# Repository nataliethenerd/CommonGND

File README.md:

# CommonGND
These are for PERSONAL USE ONLY. Free use in any personal project.
<br>My logo must be kept on the boards and on any boards adapted with them and full credit must be given. AKA read the licence (https://creativecommons.org/licenses/by-nc-sa/3.0/)
<br>Enjoy :)

## New Gameboy Pocket IO Boards
> Contribution Added by [@32teeth](https://github.com/32teeth) from [@retro-esp32](https://github.com/retro-esp32)

See [Licence](LICENCE.md) and [Code of Conduct](CODE_OF_CONDUCT.md)

| |W/O Audio | Audio |
|-|-|-|
|Top | | |
|Bottom | | |

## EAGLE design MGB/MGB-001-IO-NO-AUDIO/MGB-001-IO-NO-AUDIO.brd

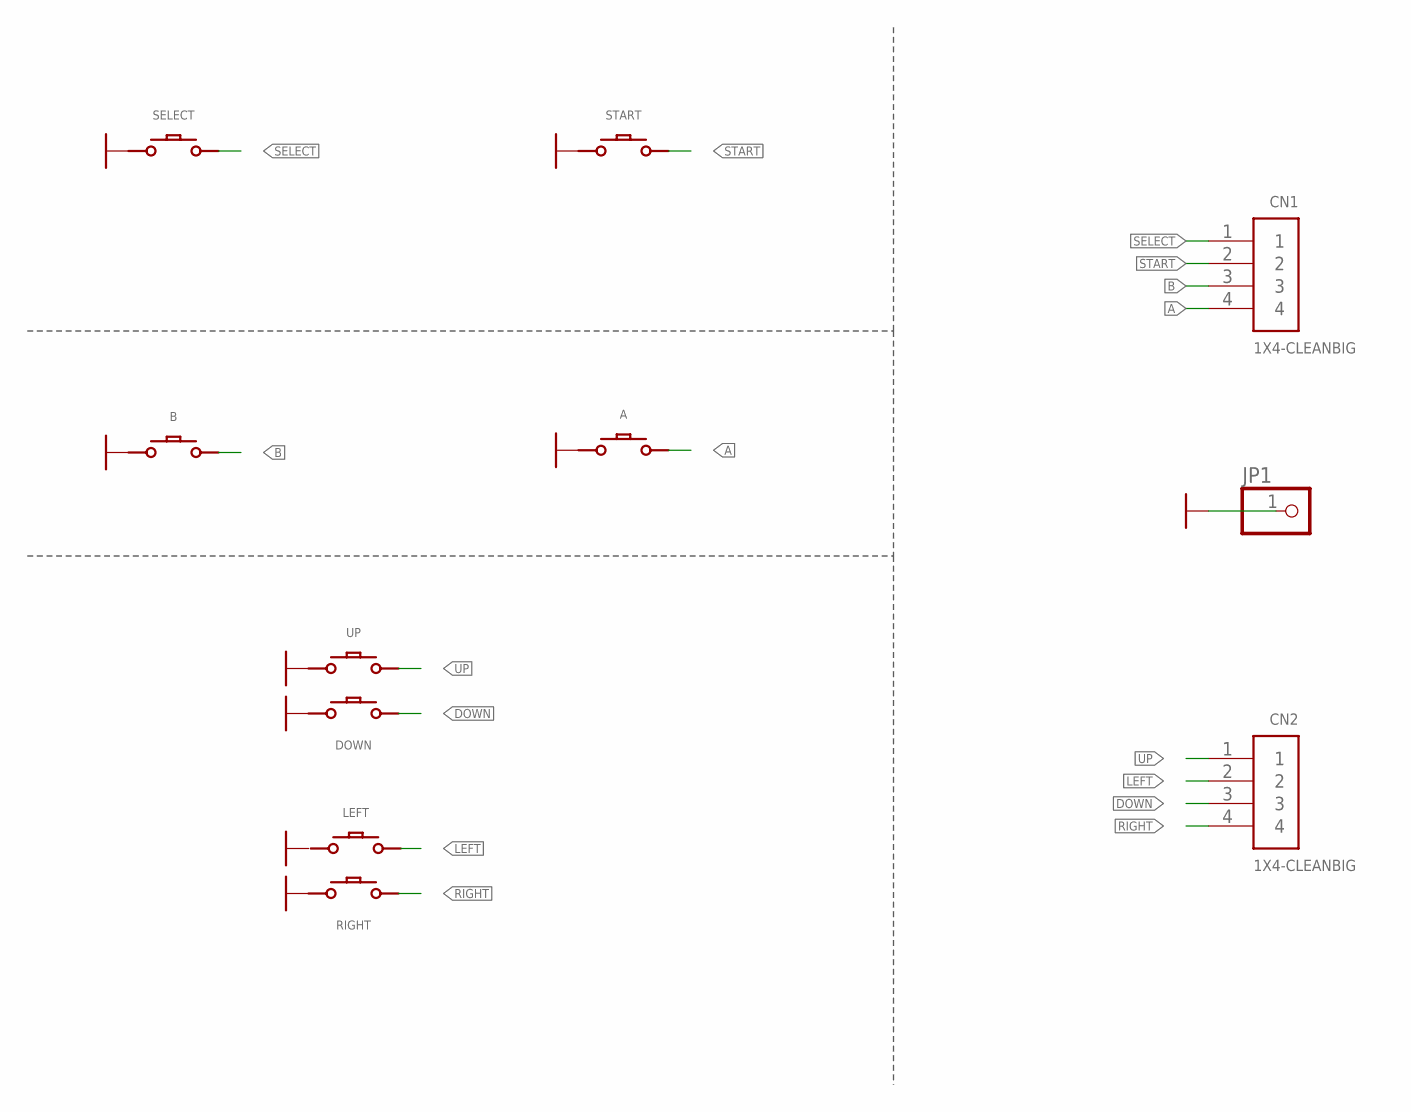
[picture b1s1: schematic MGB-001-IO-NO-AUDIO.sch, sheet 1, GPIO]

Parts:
A: CONDUCTIVE_BUTTONCONDUCTIVE_BUTTON_THICK; CONDUCTIVE_BUTTON_THICK
B: CONDUCTIVE_BUTTONCONDUCTIVE_BUTTON_THICK; CONDUCTIVE_BUTTON_THICK
CN1, CN2: 1X4-CLEANBIG; 1X04-CLEANBIG
DOWN: CONDUCTIVE_BUTTONCONDUCTIVE_BUTTON_DIRECTIONAL_TH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; CONDUCTIVE_BUTTON_DIRECTIONAL_THICK
JP1: PINHD-1X1CB; 1X01-CLEANBIG
LEFT: CONDUCTIVE_BUTTONCONDUCTIVE_BUTTON_DIRECTIONAL_TH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; CONDUCTIVE_BUTTON_DIRECTIONAL_THICK
RIGHT: CONDUCTIVE_BUTTONCONDUCTIVE_BUTTON_DIRECTIONAL_TH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; CONDUCTIVE_BUTTON_DIRECTIONAL_THICK
SELECT: CONDUCTIVE_BUTTON_STARTSELECTCONDUCTIVE_BUTTON_TH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; CONDUCTIVE_BUTTON_THICK_STARTSELECT
START: CONDUCTIVE_BUTTON_STARTSELECTCONDUCTIVE_BUTTON_TH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; CONDUCTIVE_BUTTON_THICK_STARTSELECT
UP: CONDUCTIVE_BUTTONCONDUCTIVE_BUTTON_DIRECTIONAL_TH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; CONDUCTIVE_BUTTON_DIRECTIONAL_THICK

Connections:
A: A.P$ACTIVE, CN1.4
B: B.P$ACTIVE, CN1.3
DOWN: CN2.3, DOWN.P$ACTIVE
GND: A.P$GND, B.P$GND, DOWN.P$GND, JP1.1, RIGHT.P$GND, SELECT.P$GND, SELECT.P$GND1 (P$GND), SELECT.P$GND2 (P$GND), SELECT.P$GND3 (P$GND), START.P$GND, START.P$GND1 (P$GND), START.P$GND2 (P$GND), START.P$GND3 (P$GND), UP.P$GND
LEFT: CN2.2, LEFT.P$ACTIVE
RIGHT: CN2.4, RIGHT.P$ACTIVE
SELECT: CN1.1, SELECT.P$ACTIVE, SELECT.P$ACTIVE1 (P$ACTIVE), SELECT.P$ACTIVE2 (P$ACTIVE), SELECT.P$ACTIVE3 (P$ACTIVE), SELECT.P$ACTIVE4 (P$ACTIVE), SELECT.P$ACTIVE5 (P$ACTIVE), SELECT.P$ACTIVE6 (P$ACTIVE)
START: CN1.2, START.P$ACTIVE, START.P$ACTIVE1 (P$ACTIVE), START.P$ACTIVE2 (P$ACTIVE), START.P$ACTIVE3 (P$ACTIVE), START.P$ACTIVE4 (P$ACTIVE), START.P$ACTIVE5 (P$ACTIVE), START.P$ACTIVE6 (P$ACTIVE)
UP: CN2.1, UP.P$ACTIVE

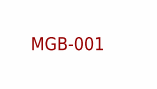
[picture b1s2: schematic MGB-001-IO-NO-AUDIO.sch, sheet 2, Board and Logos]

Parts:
U$17: MGB-001MGB-001-IO-NO-AUDIO; MGB-001-IO-NO-AUDIO

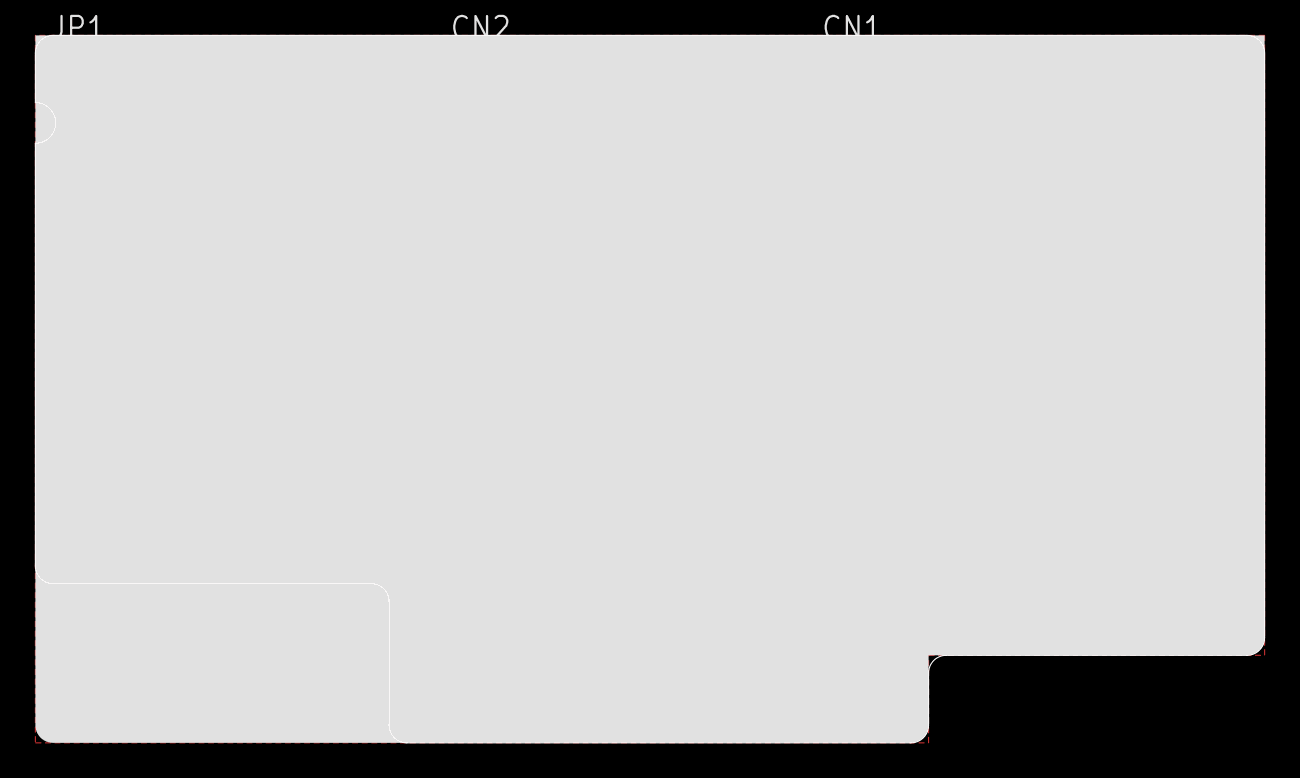
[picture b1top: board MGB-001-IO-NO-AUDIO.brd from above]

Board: 2 copper layers, 69.5 x 40.0 mm, 12 parts (0 on the bottom side), 9 nets.

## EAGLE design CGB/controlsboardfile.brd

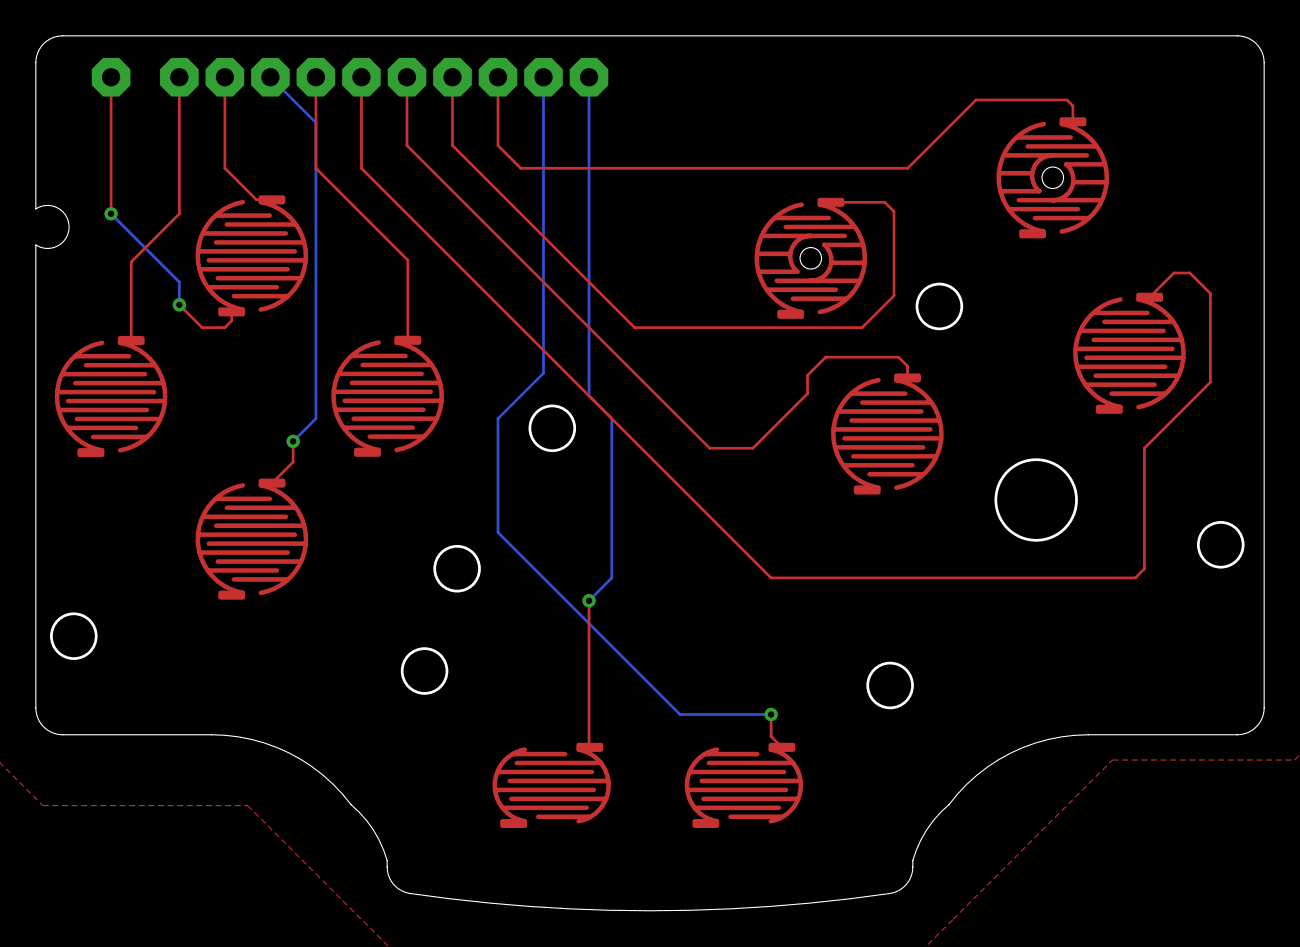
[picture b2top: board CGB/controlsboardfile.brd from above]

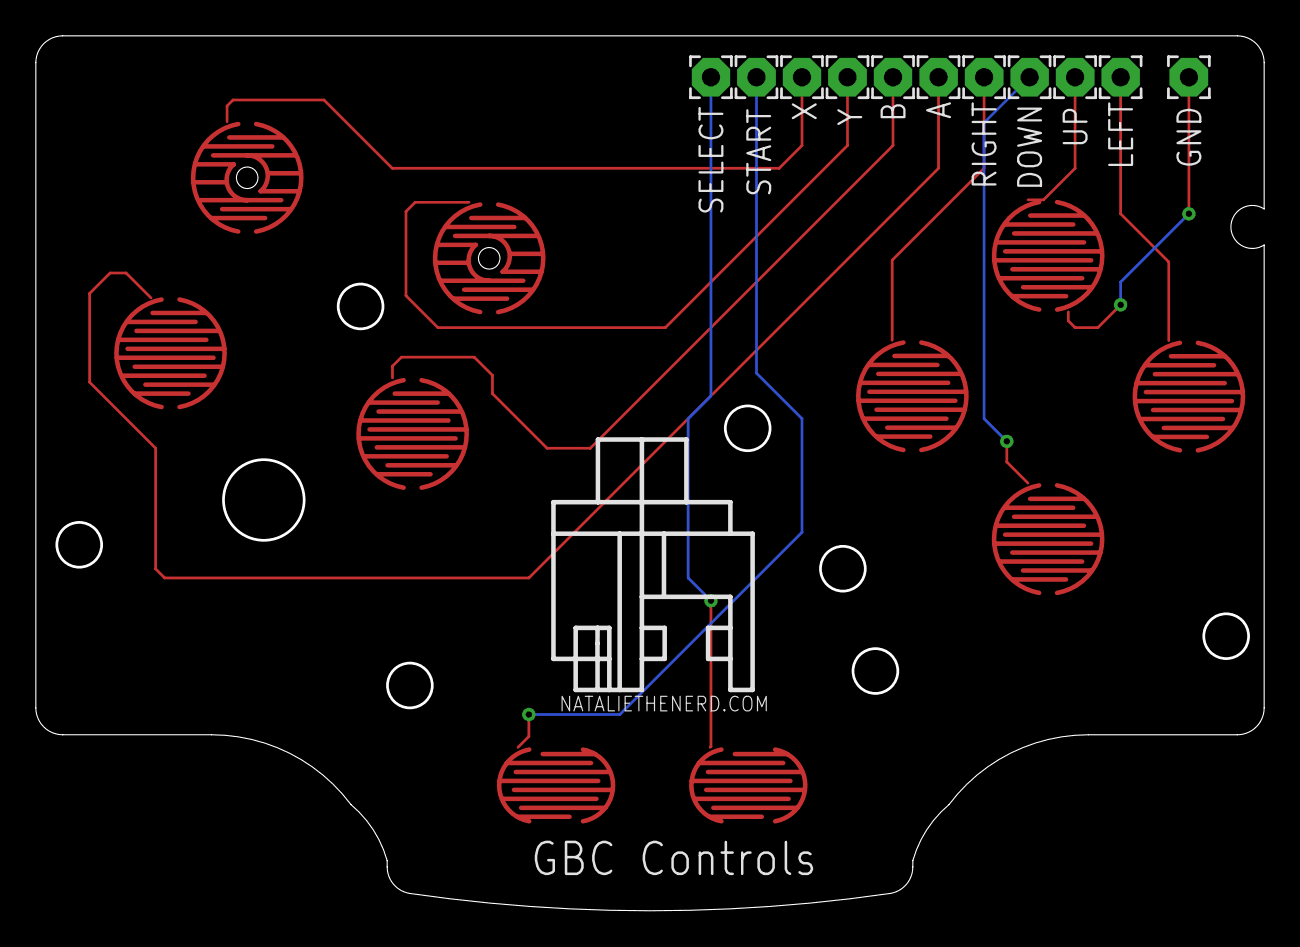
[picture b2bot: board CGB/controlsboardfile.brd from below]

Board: 2 copper layers, 68.4 x 48.7 mm, 22 parts (12 on the bottom side), 10 nets.

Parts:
A: 2,15/1,0
APAD: CONDUCTIVE_BUTTON
B: 2,15/1,0
BPAD: CONDUCTIVE_BUTTON
DOWN: 2,15/1,0
DOWNPAD: CONDUCTIVE_BUTTON
GND: 2,15/1,0
LEFT: 2,15/1,0
LEFTPAD: CONDUCTIVE_BUTTON
RIGHT: 2,15/1,0
RIGHTPAD: CONDUCTIVE_BUTTON
SELECT: 2,15/1,0
SELECTPAD: CONDUCTIVE_BUTTON_STARTSELECT
START: 2,15/1,0
STARTPAD: CONDUCTIVE_BUTTON_STARTSELECT
U$1: NEWLOGO
UP: 2,15/1,0
UPPAD: CONDUCTIVE_BUTTON
X: 2,15/1,0
XPAD: CONDUCTIVE_BUTTON_DRILL
Y: 2,15/1,0
YPAD: CONDUCTIVE_BUTTON_DRILL

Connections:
GND: APAD.P$GND, BPAD.P$GND, DOWNPAD.P$GND, GND.1, LEFTPAD.P$GND, RIGHTPAD.P$GND, SELECTPAD.P$GND, STARTPAD.P$GND, UPPAD.P$GND, XPAD.P$GND, YPAD.P$GND
unnamed: LEFT.1, LEFTPAD.P$ACTIVE
unnamed: DOWN.1, DOWNPAD.P$ACTIVE
unnamed: RIGHT.1, RIGHTPAD.P$ACTIVE
unnamed: UP.1, UPPAD.P$ACTIVE
unnamed: B.1, BPAD.P$ACTIVE
unnamed: Y.1, YPAD.P$ACTIVE
unnamed: START.1, STARTPAD.P$ACTIVE
unnamed: SELECT.1, SELECTPAD.P$ACTIVE
Y: X.1, XPAD.P$ACTIVE

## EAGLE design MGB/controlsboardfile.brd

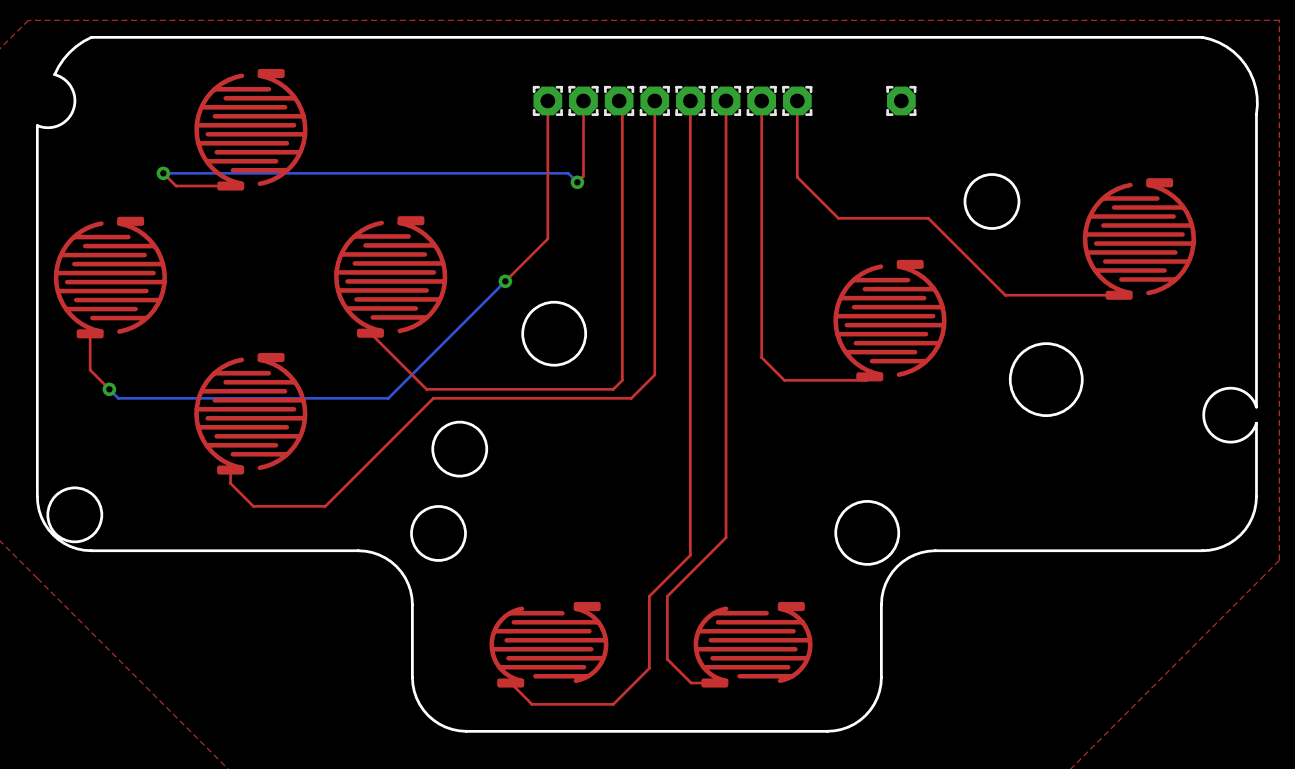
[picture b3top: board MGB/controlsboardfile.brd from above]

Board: 2 copper layers, 67.8 x 38.6 mm, 18 parts (1 on the bottom side), 9 nets.

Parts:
A: 1,6/0,8
B: 1,6/0,8
DOWN: 1,6/0,8
GND: 1,6/0,8
LEFT: 1,6/0,8
RIGHT: 1,6/0,8
SELECT: 1,6/0,8
START: 1,6/0,8
U$1, U$2, U$3, U$4, U$5, U$6: CONDUCTIVE_BUTTON
U$7, U$8: CONDUCTIVE_BUTTON_STARTSELECT
U$9: NEWLOGO
UP: 1,6/0,8

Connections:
GND: GND.1, U$1.P$ACTIVE, U$2.P$ACTIVE, U$3.P$ACTIVE, U$4.P$ACTIVE, U$5.P$ACTIVE, U$6.P$ACTIVE, U$7.P$ACTIVE, U$8.P$ACTIVE
unnamed: RIGHT.1, U$5.P$GND
unnamed: DOWN.1, U$6.P$GND
unnamed: SELECT.1, U$7.P$GND
unnamed: START.1, U$8.P$GND
unnamed: LEFT.1, U$3.P$GND
unnamed: A.1, U$2.P$GND
unnamed: B.1, U$1.P$GND
unnamed: U$4.P$GND, UP.1

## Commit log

2021-05-29 adding files
2021-05-29 transparent
2021-05-31 fixed for eagle
    added polygon outline for gnd pour
2021-05-31 small brain me made a mistake in committing these
2022-01-21 Fri 21 Jan 2022 09:27:29 EST @32teeth adding new context to IO boards for Gameboy Pocket (pre pull request)
2022-01-21 Fri 21 Jan 2022 09:51:07 EST @32teeth added library
2022-01-30 Sat 29 Jan 2022 19:18:36 EST - @32teeth added additional GND plan via, @retro-esp32 commit for PR
